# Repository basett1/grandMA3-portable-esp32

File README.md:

# 🎛️ Portable MAesp32 — Wireless Pocket Remote & Ethernet OSC Bridge for GrandMA3

> 🌐 **Lingua / Language**: **🇮🇹 Italiano** | **[🇬🇧 English](./README_EN.md)**

-brightgreen?style=for-the-badge)

**Portable MAesp32** è un sistema di controllo remoto tascabile, bidirezionale e a bassissima latenza progettato per le console luci **GrandMA3** (e sistemi onPC).  
Permette a Lighting Designer, programmatori e tecnici di palco di puntare i fari (*focusing*), richiamare gruppi, lanciare Cue/Sequenze e gestire Highlight/Solo muovendosi liberamente sul palco **senza bisogno di alcuna rete Wi-Fi esterna o router dedicato**.

---

## ✨ Perché Portable MAesp32?

Durante il *focus* o il *rigging* in teatro, arena o festival, collegare tablet o smartphone via Wi-Fi alla rete di regia presenta tre problemi classici:
1. **Saturazione RF e disconnessioni** quando il locale si riempie o il telefono va in blocco schermo.
2. **Mancanza di tasti rapidi dedicati** con feedback immediato sotto le dita.
3. **Configurazione di rete complessa** (DHCP, access point esterni, indirizzi IP che cambiano).

**Portable MAesp32** risolve tutto dividendo l'architettura in due unità dedicate che parlano tra loro in **ESP-NOW diretto peer-to-peer (~1 ms di latenza)**:
- 🟣 **Unità VIOLA (Bridge Ethernet <-> ESP-NOW)**: rimane in regia o vicino allo switch di rete, collegata via cavo RJ45 Ethernet alla console **GrandMA3** su PCB custom dedicata (`ESP_ETH`).
- 🟡 **Unità GIALLA (Controller Touch CYD)**: telecomando tascabile basato su **ESP32-2432S028** con display touch TFT da 2.8" (320×240), LED RGB di stato e 6 schermate operative.

---

## 🏗️ Architettura del Sistema

```mermaid
flowchart LR
    subgraph PALCO ["🎤 Sul Palco (Wireless P2P)"]
        CYD["🟡 Unità GIALLA (CYD)\nESP32-2432S028 Touch 2.8''\n6 Pagine UI + Standby Auto"]
    end

    subgraph REGIA ["🎛️ In Regia / FOH (Cablato)"]
        BRIDGE["🟣 Unità VIOLA (Bridge)\nESP32-S3 + W5500 SPI\nOLED 72x40 + Custom PCB"]
        MA3["💻 Console GrandMA3 / onPC\nServer OSC UDP (Porta 8000)"]
    end

    CYD -- "Comandi / Ping / Config IP\n(ESP-NOW 2.4GHz ~1ms)" --> BRIDGE
    BRIDGE -- "ACK Link + Nomi 40 Gruppi\n(ESP-NOW 2.4GHz)" --> CYD
    BRIDGE -- "Pacchetti OSC (/cmd ,s) + Inline Lua\nEthernet RJ45" --> MA3
    MA3 -- "Zero-Plugin SendOSC Feedback\nUDP/OSC (40 Gruppi)" --> BRIDGE
```

---

## 📂 Struttura del Repository

```text
portable MAesp32/
├── README.md                                 # Documentazione tecnica e guida d'uso
├── PRESENTATION.md                           # Presentazione del progetto per GitHub / Showcase
├── LICENSE                                   # Licenza Open Source MIT
├── firmware/
│   ├── MA3_ESPNOW_VIOLA_V3/
│   │   └── MA3_ESPNOW_VIOLA_V3.ino           # Firmware Bridge (ESP32-S3 + W5500 + OLED 72x40)
│   └── MA3_ESPNOW_CYB_V3/
│       └── MA3_ESPNOW_CYB_V3.ino             # Firmware Controller Touch (ESP32-2432S028 CYD)
└── hardware/
    ├── kicad/                                # Progetto KiCad 9.0 completo + modelli 3D (.step / .3mf)
    │   ├── ESP_ETH.kicad_pro
    │   ├── ESP_ETH.kicad_sch
    │   ├── ESP_ETH.kicad_pcb
    │   ├── ESP_ETH.3mf
    │   └── ESP_ETH.step
    └── gerber/                               # File Gerber pronti per la produzione (JLCPCB / PCBWay)
        ├── ESP_ETH_Gerber.zip
        └── *.gbr / *.gbrjob
```

---

## 🖥️ Le 6 Pagine dell'Unità GIALLA (Controller CYD)

| Pagina | Nome | Funzioni e Scorciatoie |
| :---: | :--- | :--- |
| **P1** | **Tastierino Canali** | Tastierino numerico completo (`0–9`, `.`, `+`, `Thru`, `At`, `CLR`, `PLEASE`).<br>• **Doppio Tap su `+`**: invia subito `At Percent + 10`<br>• **Doppio Tap su `At`**: invia subito `<Selezione> At Normal` (Full/Normal)<br>• **Doppio Tap su `.`**: invia subito `<Selezione> At 0` |
| **P2** | **Utility & Focus** | Tasti rapidi giganti per il puntamento luci:<br>• `NEXT` / `PREV` per scorrere le fixture<br>• `HIGHLIGHT` (toggle On/Off con stato visivo arancione)<br>• `SOLO` (toggle On/Off con stato visivo blu)<br>• `CLEAR` immediato |
| **P3** | **Cue & Sequence** | Tastierino dedicato al playback: `GOTO`, `CUE`, `SEQ`, `0–9`, `.`, `CLR`, `PLEASE`. |
| **P4** | **Database 40 Gruppi** | Griglia paginata per **40 Gruppi** (`6` per schermata, scorrimento `<<` e `>>`).<br>• Tasto **`SYNC NAMES` (Zero-Plugin!)**: il Bridge inietta direttamente via `/cmd` uno script **Inline Lua** a 8 micro-batch su GrandMA3, auto-configura l'IP di ritorno OSC e riceve in tempo reale i veri nomi dei 40 gruppi dalla console **senza dover installare alcun plugin nello showfile**! |
| **P5** | **Rete & IP Remoto** | Configurazione diretta di **Local IP (Bridge)**, **Target IP (MA3)** e **OSC Port**.<br>• Supporta **Auto-Repeat accelerato** tenendo premuto `+` o `-`.<br>• Premendo **`SAVE SETTINGS`**, salva in NVS e aggiorna via radio anche il Bridge Viola! |
| **P6** | **Backlight & Power** | Regolazione della luminosità del display su **10 livelli (`0% – 100%`)** salvata in memoria NVS.<br>• **Standby automatico dopo 30s** di inattività (0% consumi backlight) con risveglio al primo tocco (senza premere tasti per errore). |

---

## 🔌 Hardware & Pinout

### 1. Unità VIOLA — Bridge Ethernet (`ESP32-S3 + W5500 + OLED 0.42"`)
Realizzata su **PCB custom dedicata** (file KiCad e Gerber inclusi in [`hardware/`](./hardware)).

| Componente / Segnale | Pin ESP32-S3 | Note Tecniche |
| :--- | :---: | :--- |
| **W5500 SPI SCK** | `GPIO 4` | Clock bus SPI Ethernet |
| **W5500 SPI MISO** | `GPIO 1` | Master In Slave Out |
| **W5500 SPI MOSI** | `GPIO 7` | Master Out Slave In |
| **W5500 SPI CS (SCS)** | `GPIO 3` | Chip Select Ethernet |
| **OLED 72×40 I2C SCL** | `GPIO 6` | Display integrato SSD1306 (Full-Buffer `_F_`) |
| **OLED 72×40 I2C SDA** | `GPIO 5` | Display integrato SSD1306 |
| **Tasto Pagina OLED** | `GPIO 9` | Tasto `BOOT` integrato (cicla tra `BR-IP`, `MA-IP`, `PORT`, `CYB-STAT`) |

### 2. Unità GIALLA — Controller Touch (`ESP32-2432S028 CYD`)
Nessuna saldatura richiesta: utilizza la scheda standard *Cheap Yellow Display* da 2.8".

| Periferica CYD | Pin ESP32 | Note Tecniche |
| :--- | :---: | :--- |
| **Touch XPT2046 SPI** | `CLK 25`, `MISO 39`, `MOSI 32` | Bus `VSPI` dedicato al controller touch resistivo |
| **Touch CS / IRQ** | `CS 33`, `IRQ 36` | Chip Select e Interrupt Touch |
| **Backlight PWM** | `GPIO 21` | Controllo PWM a 10 livelli + spegnimento Standby |
| **LED RGB Onboard** | `R: 4`, `G: 16`, `B: 17` | Feedback luminoso non bloccante (Active-Low) |

---

## 🛠️ Produzione PCB (`hardware/`)

Nella cartella [`hardware/`](./hardware) trovi tutto il necessario per produrre la scheda **ESP_ETH** dell'unità Bridge:
- **Gerber pronti per la stampa**: carica direttamente [`hardware/gerber/ESP_ETH_Gerber.zip`](./hardware/gerber/ESP_ETH_Gerber.zip) su **JLCPCB**, **PCBWay** o **Aisler** (2 layer standard, spessore 1.6 mm, finitura HASL/ENIG).
- **Sorgenti KiCad 9.0**: schema elettrico ([`ESP_ETH.kicad_sch`](./hardware/kicad/ESP_ETH.kicad_sch)) e layout PCB ([`ESP_ETH.kicad_pcb`](./hardware/kicad/ESP_ETH.kicad_pcb)).
- **Modelli 3D**: file [`ESP_ETH.step`](./hardware/kicad/ESP_ETH.step) e [`ESP_ETH.3mf`](./hardware/kicad/ESP_ETH.3mf) per progettare o stampare in 3D un case su misura.

---

## 🚀 Configurazione su GrandMA3

1. **Collegamento di Rete**:
   - Collega l'unità **VIOLA** via cavo Ethernet allo stesso switch della console GrandMA3 (o del PC con GrandMA3 onPC).
   - Dalla **Pagina 5** dell'unità **GIALLA**, imposta:
     - `LOCAL IP (BRIDGE)`: un IP libero nella sottorete di MA3 (es. `192.168.1.100`)
     - `TARGET IP (MA3)`: l'IP della console GrandMA3 (es. `192.168.1.223`)
     - `OSC PORT`: `8000` (o la porta impostata su MA3)
   - Premi **`SAVE SETTINGS`**: il Bridge salverà i parametri in memoria permanente e si riavvierà con il nuovo IP.

2. **Abilitazione OSC su GrandMA3**:
   - Vai in **Menu → In & Out → OSC**.
   - Nella riga **OSCData 1**, imposta:
     - **Destination IP**: `192.168.1.100` *(IP del Bridge Viola)*
     - **Mode**: `UDP`
     - **Port**: `8000`
     - **Receive**: `Yes`
     - **Receive Command**: `Yes`
     - **Send**: `Yes`
     - **Enabled**: `Yes`

3. **Sincronizzazione 40 Gruppi "Zero-Plugin" & Auto-Creazione Riga OSC Non Distruttiva**:
   - **Non serve creare o importare alcun Plugin nello showfile di GrandMA3, né rischiare di sovrascrivere linee OSC già usate (es. QLab, Companion, Timecode)!**
   - Quando premi **`SYNC NAMES`** nella **Pagina 4** del controller tascabile:
     1. **Auto-Discovery / Append Non Distruttivo (`_G.MAESP`)**: il Bridge **VIOLA** invia un comando `Lua "..."` inline su `/cmd` che scansiona `ShowData().OSCBase`:
        - Se trova già una riga chiamata **`MAesp32`** (o che punta già all'IP del Bridge), **riusa quella riga** senza creare duplicati.
        - Se `OSC 1`, `OSC 2`, ecc. sono già occupate da altri sistemi, **non le tocca**: chiama `:Append()` creando una **nuova riga dedicata in coda** chiamata **`MAesp32`** con `DestinationIP` = IP del Bridge, `Port` = porta configurata e `Send = Yes`, salvandone l'indice in `_G.MAESP`.
     2. **Scansione a 8 Micro-Batch**: subito dopo, il Bridge interroga `DataPool().Groups[1..40]` in **8 micro-batch da 5 gruppi ogni 75 ms** inviando `SendOSC <_G.MAESP>` verso la riga dedicata appena trovata/creata.
     3. I primi 40 gruppi dello showfile compaiono in meno di mezzo secondo sui pulsanti touch del palmare!

---

## ⚙️ Miglioramenti Tecnici della Versione V3 PRO

- **Coda FreeRTOS Thread-Safe (`rxQueue`)**: sull'unità Viola la ricezione radio ESP-NOW (`OnDataRecv`, Core 0) è completamente disaccoppiata dal bus SPI del modulo Ethernet W5500 (Core 1), eliminando qualsiasi rischio di collisione SPI durante il traffico bidirezionale simultaneo.
- **Display OLED Full-Buffer (`_F_`) non bloccante**: il display 72×40 della Viola viene aggiornato in RAM (360 byte) e inviato via I2C ogni 60 ms senza cicli `firstPage()/nextPage()` né `delay()`, lasciando la CPU libera al 99% per processare raffiche di pacchetti UDP da MA3.
- **Zero Frammentazione Heap**: sostituiti gli array dinamici `String` dei 40 gruppi con buffer statici pre-allocati (`char groupNames[40][20]`) e parsing `char*` in `OnDataRecv` senza alcun `delay()`.
- **Touch State Machine + Auto-Repeat**: rilevamento sul fronte di salita del tocco (niente più tocchi multipli involontari tenendo premuto il dito), doppi click rapidi su `+` / `At` / `.` e scorrimento veloce tenendo premuto `+` o `-` nella configurazione IP/Porta.
- **Ridisegno Parziale Flicker-Free**: nella Pagina 5 (IP/Porta) e Pagina 6 (Backlight) vengono ridisegnate solo le caselle numeriche modificate, eliminando lo sfarfallio a tutto schermo.
- **Isolamento Salvataggio Luminosità**: la modifica della luminosità salva in NVS solo il parametro locale senza inviare il comando di reboot al Bridge Ethernet.

---

## 👤 Autore & Licenza

Progettato e sviluppato da **Angelo Parlato**.  
Rilasciato sotto licenza [MIT](./LICENSE) — sentiti libero di studiare, costruire e personalizzare il tuo **Portable MAesp32**!

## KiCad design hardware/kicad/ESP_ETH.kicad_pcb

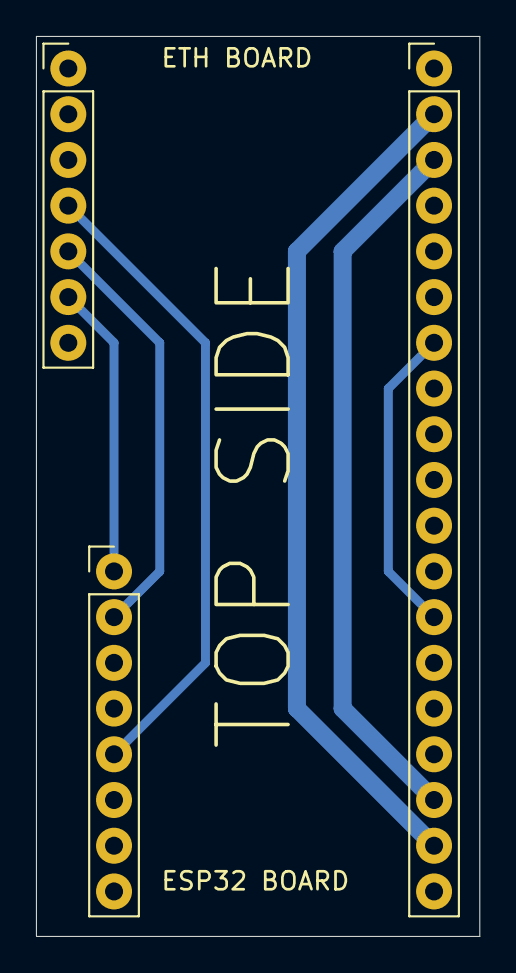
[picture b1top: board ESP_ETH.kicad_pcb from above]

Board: 2 copper layers, 24.6 x 50.0 mm, 3 parts (0 on the bottom side), 6 nets.

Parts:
ETH: ETH; PinHeader_1x07_P2.54mm_Vertical
J1: LATO SX; PinHeader_1x19_P2.54mm_Vertical
J3: ESP32; PinHeader_1x08_P2.54mm_Vertical

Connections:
unnamed: J1.7, J1.13
unnamed: J1.3, J1.17
unnamed: J1.2, J1.18
unnamed: ETH.4, J3.5
unnamed: ETH.5, J3.2
unnamed: ETH.6, J3.1

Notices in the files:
README.md:
License: MIT
